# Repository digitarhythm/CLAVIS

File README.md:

CLAVIS

- TReK G70 CLAVIS KiCAD Project

[Firmware repository](https://github.com/digitarhythm/qmk_firmware/tree/digitarhythm/keyboards/trek/clavis)

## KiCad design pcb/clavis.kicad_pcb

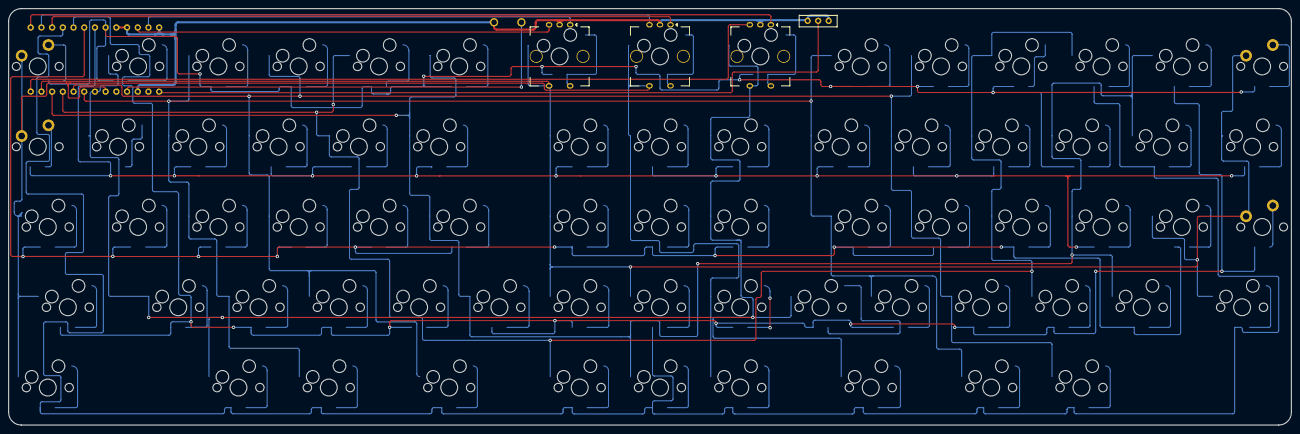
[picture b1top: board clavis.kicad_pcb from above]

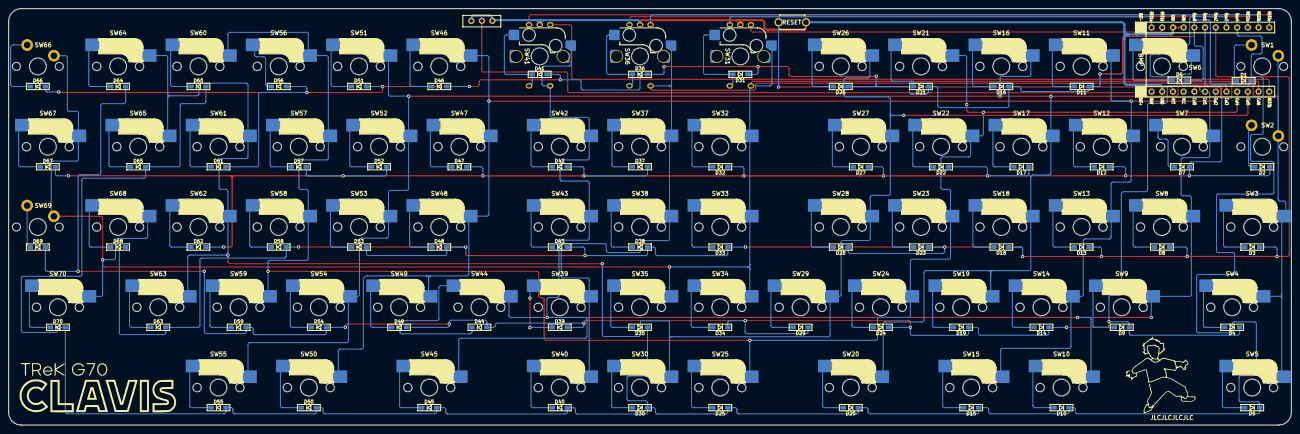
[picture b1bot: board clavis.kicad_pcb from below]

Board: 2 copper layers, 304.3 x 98.8 mm, 145 parts (2 on the bottom side), 91 nets.

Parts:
D1, D2, D3, D4, D5, D6, D7, D8, D9, D10, D11, D12, D13, D14, D15, D16, D17, D18, D19, D20, D21, D22, D23, D24, D25, D26, D27, D28, D29, D30, D31, D32, D33, D34, D35, D36, D37, D38, D39, D40, D41, D42, D43, D44, D45, D46, D47, D48, D49, D50, D51, D52, D53, D54, D55, D56, D57, D58, D59, D60, D61, D62, D63, D64, D65, D66, D67, D68, D69, D70: D; Diode_SMD
G000, G001: LOGO
J1: Conn_01x02; Battery_XH2.5_GL_PCB
SW1, SW2, SW66, SW69: SW_PUSH; CherryMX_Solder_1u_MillMax
SW3, SW15, SW50, SW67, SW68: SW_PUSH; CherryMX_Hotswap_1.25u
SW4, SW20, SW45: SW_PUSH; CherryMX_Hotswap_1.75u
SW5, SW6, SW7, SW8, SW9, SW10, SW11, SW12, SW13, SW14, SW16, SW17, SW18, SW19, SW21, SW22, SW23, SW24, SW25, SW26, SW27, SW28, SW29, SW30, SW32, SW33, SW34, SW35, SW37, SW38, SW39, SW40, SW42, SW43, SW44, SW46, SW47, SW48, SW49, SW51, SW52, SW53, SW54, SW55, SW56, SW57, SW58, SW59, SW60, SW61, SW62, SW63, SW64, SW65: SW_PUSH; CherryMX_Hotswap_1u
SW31, SW36, SW41: RotaryEncoder_Switch; SW_Cherry_MX_1.00u_Kailh_EC12
SW70: SW_PUSH; CherryMX_Hotswap_1.5u
SW81: SW_PUSH; ResetSW
U1: BLEMicroPro; Micon_BMP_GL

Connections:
Bat+: J1.1, U1.25 (BAT+)
Col0: SW1.1, SW2.1, SW3.1, SW4.1, SW5.1, SW36.S2, SW37.1, SW38.1, SW39.1, SW40.1, U1.20 (F4/PIN20)
Col1: SW6.1, SW7.1, SW8.1, SW9.1, SW10.1, SW41.S2, SW42.1, SW43.1, SW44.1, SW45.1, U1.19 (F5/PIN19)
Col2: SW11.1, SW12.1, SW13.1, SW14.1, SW15.1, SW46.1, SW47.1, SW48.1, SW49.1, SW50.1, U1.18 (F6/PIN18)
Col3: SW16.1, SW17.1, SW18.1, SW19.1, SW20.1, SW51.1, SW52.1, SW53.1, SW54.1, SW55.1, U1.17 (F7/PIN17)
Col4: SW21.1, SW22.1, SW23.1, SW24.1, SW25.1, SW56.1, SW57.1, SW58.1, SW59.1, SW60.1, U1.16 (B1/PIN16)
Col5: SW26.1, SW27.1, SW28.1, SW29.1, SW30.1, SW61.1, SW62.1, SW63.1, SW64.1, SW65.1, U1.15 (B3/PIN15)
Col6: SW31.S2, SW32.1, SW33.1, SW34.1, SW35.1, SW66.1, SW67.1, SW68.1, SW69.1, SW70.1, U1.14 (B2/PIN14)
GND: J1.2, SW31.C, SW36.C, SW41.C, SW81.2, U1.3 (GND), U1.4 (GND), U1.23 (GND), U1.26 (BAT-)
unnamed: D1.2 (A), SW1.2
unnamed: D2.2 (A), SW2.2
unnamed: D3.2 (A), SW3.2
unnamed: D4.2 (A), SW4.2
unnamed: D5.2 (A), SW5.2
unnamed: D6.2 (A), SW6.2
unnamed: D7.2 (A), SW7.2
unnamed: D8.2 (A), SW8.2
unnamed: D9.2 (A), SW9.2
unnamed: D10.2 (A), SW10.2
unnamed: D11.2 (A), SW11.2
unnamed: D12.2 (A), SW12.2
unnamed: D13.2 (A), SW13.2
unnamed: D14.2 (A), SW14.2
unnamed: D15.2 (A), SW15.2
unnamed: D16.2 (A), SW16.2
unnamed: D17.2 (A), SW17.2
unnamed: D18.2 (A), SW18.2
unnamed: D19.2 (A), SW19.2
unnamed: D20.2 (A), SW20.2
unnamed: D21.2 (A), SW21.2
unnamed: D22.2 (A), SW22.2
unnamed: D23.2 (A), SW23.2
unnamed: D24.2 (A), SW24.2
unnamed: D25.2 (A), SW25.2
unnamed: D26.2 (A), SW26.2
unnamed: D27.2 (A), SW27.2
unnamed: D28.2 (A), SW28.2
unnamed: D29.2 (A), SW29.2
unnamed: D30.2 (A), SW30.2
unnamed: D31.2 (A), SW31.S1
unnamed: D32.2 (A), SW32.2
unnamed: D33.2 (A), SW33.2
unnamed: D34.2 (A), SW34.2
unnamed: D35.2 (A), SW35.2
unnamed: D36.1 (K), SW36.S1
unnamed: D37.1 (K), SW37.2
unnamed: D38.1 (K), SW38.2
unnamed: D39.1 (K), SW39.2
unnamed: D40.1 (K), SW40.2
unnamed: D41.1 (K), SW41.S1
unnamed: D42.1 (K), SW42.2
unnamed: D43.1 (K), SW43.2
unnamed: D44.1 (K), SW44.2
unnamed: D45.1 (K), SW45.2
unnamed: D46.1 (K), SW46.2
unnamed: D47.1 (K), SW47.2
unnamed: D48.1 (K), SW48.2
unnamed: D49.1 (K), SW49.2
unnamed: D50.1 (K), SW50.2
unnamed: D51.1 (K), SW51.2
unnamed: D52.1 (K), SW52.2
unnamed: D53.1 (K), SW53.2
unnamed: D54.1 (K), SW54.2
unnamed: D55.1 (K), SW55.2
unnamed: D56.1 (K), SW56.2
unnamed: D57.1 (K), SW57.2
unnamed: D58.1 (K), SW58.2
unnamed: D59.1 (K), SW59.2
unnamed: D60.1 (K), SW60.2
unnamed: D61.1 (K), SW61.2
unnamed: D62.1 (K), SW62.2
unnamed: D63.1 (K), SW63.2
unnamed: D64.1 (K), SW64.2
unnamed: D65.1 (K), SW65.2
unnamed: D66.1 (K), SW66.2
unnamed: D67.1 (K), SW67.2
unnamed: D68.1 (K), SW68.2
unnamed: D69.1 (K), SW69.2
unnamed: D70.1 (K), SW70.2
RE01a: SW31.A, U1.1 (D3/PIN1)
RE01b: SW31.B, U1.2 (D2/PIN2)
RE02a: SW36.A, U1.10 (E6/PIN10)
RE02b: SW36.B, U1.11 (B4/PIN11)
RE03a: SW41.A, U1.12 (B5/PIN12)
RE03b: SW41.B, U1.13 (B6/PIN13)
Reset: SW81.1, U1.22 (RST)
Row0: D1.1 (K), D6.1 (K), D11.1 (K), D16.1 (K), D21.1 (K), D26.1 (K), D31.1 (K), D36.2 (A), D41.2 (A), D46.2 (A), D51.2 (A), D56.2 (A), D61.2 (A), D66.2 (A), U1.5 (D1/PIN5/SDA)
Row1: D2.1 (K), D7.1 (K), D12.1 (K), D17.1 (K), D22.1 (K), D27.1 (K), D32.1 (K), D37.2 (A), D42.2 (A), D47.2 (A), D52.2 (A), D57.2 (A), D62.2 (A), D67.2 (A), U1.6 (D0/PIN6/SCL)
Row2: D3.1 (K), D8.1 (K), D13.1 (K), D18.1 (K), D23.1 (K), D28.1 (K), D33.1 (K), D38.2 (A), D43.2 (A), D48.2 (A), D53.2 (A), D58.2 (A), D63.2 (A), D68.2 (A), U1.7 (D4/PIN7)
Row3: D4.1 (K), D9.1 (K), D14.1 (K), D19.1 (K), D24.1 (K), D29.1 (K), D34.1 (K), D39.2 (A), D44.2 (A), D49.2 (A), D54.2 (A), D59.2 (A), D64.2 (A), D69.2 (A), U1.8 (C6/PIN8)
Row4: D5.1 (K), D10.1 (K), D15.1 (K), D20.1 (K), D25.1 (K), D30.1 (K), D35.1 (K), D40.2 (A), D45.2 (A), D50.2 (A), D55.2 (A), D60.2 (A), D65.2 (A), D70.2 (A), U1.9 (D7/PIN9)

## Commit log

2024-01-30 update Licence file
2024-02-25 Update LICENCE
